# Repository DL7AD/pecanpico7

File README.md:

# Pecan Pico 7 Balloon Tracker

Pecan Pico 7 is an APRS & SSDV Tracker based on the STM32F429 microcontroller. Please note that this PCB is untested.

Components
==========

| Component                  | Description            | Purpose on PCB
| -------------------------- | ---------------------- | ----------------------------
| [**Camera OV9655 option**](https://raw.githubusercontent.com/DL7AD/pecanpico7/master/export/sch_camera.png?token=AFbk8RzoP9qTo4VENojvSboy-pLNPzOqks5Wddq2wA%3D%3D)
| TI TC1185-1.8VCT713        | LDO                    | Generate camera core voltage
| OmniVision OV9655          | Camera                 | Taking pictures
| [**Camera OV2640 option**](https://raw.githubusercontent.com/DL7AD/pecanpico7/master/export/sch_camera.png?token=AFbk8RzoP9qTo4VENojvSboy-pLNPzOqks5Wddq2wA%3D%3D)
| TI LP5951MF-1.3/NOPB       | LDO                    | Generate camera core voltage
| OmniVision OV2640          | Camera                 | Taking pictures
| [**Clock**](https://raw.githubusercontent.com/DL7AD/pecanpico7/master/export/sch_clock.png?token=AFbk8UbgKZMbE2NQFpeVvyRg0LgJKIOcks5WddrcwA%3D%3D)
| Epson TG-5006CJ-19H        | TCXO 26MHz             | Generate clock for STM32 and transceivers
| [**GNSS**](https://raw.githubusercontent.com/DL7AD/pecanpico7/master/export/sch_gps.png?token=AFbk8dw5krbUbh26B37_rMTrtYQ4tBQFks5Wddr7wA%3D%3D)
| ublox MAX-7C               | GNSS receiver          | Receive GPS or GLONASS
| Avago ALM-GP003            | Preamplifier           | Filters and preamplifies GNSS signal
| [**IO**](https://raw.githubusercontent.com/DL7AD/pecanpico7/master/export/sch_io.png?token=AFbk8fbugmLABbDKRANGqdMaBevwF8SGks5WddsRwA%3D%3D)
| *not specified*            | microSD card           | Flash memory (take any microSD card whatever you want)
| [**Micro Processor Unit (MPU)**](https://raw.githubusercontent.com/DL7AD/pecanpico7/master/export/sch_mpu.png?token=AFbk8bgT5gPxzDA8xYnTLKaIEUAItRCqks5WddshwA%3D%3D)
| STM32F429IIH6              | MCU                    | Controlling all actions on the PCB
| [**Power management**](https://raw.githubusercontent.com/DL7AD/pecanpico7/master/export/sch_power_management.png?token=AFbk8VZ4GDgAdff5pM0KQ5WDNG89CJzSks5Wdds4wA%3D%3D)
| ST SPV1040                 | Solar battery charger  | Charging the battery from solar cells
| TI TPS62260DRVT            | Step-Down regulator    | Step down voltage from battery to Vcc rail (2.5V)
| Microchip PAC1720-1-AIA-TR | Current/Voltage sensor | Measure battery input and output current and battery voltage
| [**Radios**](https://raw.githubusercontent.com/DL7AD/pecanpico7/master/export/sch_radios.png?token=AFbk8c2585z1ySrIXfuM0fE5kp1bYGUBks5WddtOwA%3D%3D)
| SiLabs Si4060 (Radio 1)    | Transmitter (2m)       | Transmitting on 2m with 3W
| rfmd RF6886                | Power amplifier        | Amplify singal from Radio 1
| SiLabs Si4464 (Radio 2)    | Transceiver (70cm)     | Transmit and Receive on 70cm with 10mW
| [**Sensing**](https://raw.githubusercontent.com/DL7AD/pecanpico7/master/export/sch_sensing.png?token=AFbk8bKAeUidCmY9ixlxbY80DIifiAG-ks5WddtfwA%3D%3D)
| Bosch BME280              | Airpressure sensor      | Measuring airpressure, humidity, temperature
| Invensense MPU-9250       | Power amplifier         | Measure acceleration, rotation, Earth's magnetic field

Bus connections to peripheral devices
=====================================

There are two I2C bus and one SPI and two UART buses available on the the PCB.
The SPI bus is dedicated to the SiLabs radios. One UART is connected to the GNSS
receiver while the other is available for external debugging purposes. There are
two additional I2C buses. One is used for the camera while the other is used for
everything else. This has been done to avoid routing the I2C through dense
regions on the PCB. The second bus of the I2C can be accessed by a pin header
for external peripheral devices such as an external BME280 to measure balloon
pressure.

**I2C**

| Bus | SCL  | SDA
| --- | ---- | ----
| 1   | PB8  | PB9
| 2   | PB10 | PB11

| Component                   | Bus | Address
| --------------------------- | --- | -------
| OmniVision OV9655/OV2640    | 1   | 0x30
| ublox MAX-7C                | 2   | 0x42
| Microchip PAC1720-1-AIA-TR  | 2   | 0x4C
| Bosch BME280                | 2   | 0x77
| Invensense MPU-9250         | 2   | 0x69
| External pin header         | 2   | -

**SPI**

- SPI SCK: PB13
- SPI MISO: PB14
- SPI MOSI: PB15

| Component                   | CS at STM32
| --------------------------- | -----------
| SiLabs Si4060 (Radio 1)     | PA11
| SiLabs Si4464 (Radio 2)     | PB0

**UART**

| Component           | STM32 TXD | STM32 RXD
| ------------------- | --------- | ---------
| uBlox MAX-7C        | PA2       | PA3
| External pin header | PA0       | PA1

Power feeding
=============

Since this tracker is designed for solar use, there's a solar charging chip, a
battery (LiPo) and a discharging regulator on it. The SPV1040 will charge the battery
on the back of the PCB. It will charge the battery up to 4.1V. The voltage of the
battery is then steped down to 2.5V by the TPS62260 which is fed by the battery. With
exception of the RF6886 All parts are fed by the 2.5V (Vcc) rail. The RF6886 is
connected directly to VBAT in order to get more power out of it. The PAC1720 is able
to measure the charge and discharge current of the battery.

**! PCB ERROR:** The PAC1720 can't measure the current consumed by RF6886.

The camera needs an addional voltage for the core. This must be 1.3V (OV2640) or 1.8V
(OV9655). Depending on which camera is used, IC10 must be changed (notes in schematic).
IC10 is switched by Q2 (GPS shutdown MOSFET). If the camera is switched off, IC10
does not get power as well.

Components Shutdown
===================

Every component has it's own shutdown capacility. Some components are switched off
by an additional MOSFET because when standard shutdown functions still need some mA.

| Component                  | Shutdown       | Notes
| -------------------------- | -------------- | --------------------------------------------
| Microchip PAC1720-1-AIA-TR | none           | Standby current 5.5uA
| Radio 1                    | Pull PA12 high |
| Radio 2                    | Pull PB12 high |
| rfmd RF6886                | none           |
| Bosch BME280               | none           | Standby current 0.2uA
| MPU-9250                   | none           | Idle mode 8uA
| Camera                     | Pull PE0 high  | Camera SHDN still draws 1mA
| Clock (TCXO)               | none           | Needed for STM32 all time
| GPS and GPS preAMP         | Pull PE7 high  |
| microSD card               | none           | SD cards have usually good internal shutdown
| STM32                      | none           |

Camera connection
=================

The camera is connected to the DCMI interface of the STM32F4 which can handle the
data though the microcontroller internally. The camera itself is connected to a FFC
connector on the PCB. The STM32 data pins are connected to

| STM32 Pin | Function
| --------- | ----------
| PA4       | DCMI_HSYNC
| PA6       | DCMI_PCLK
| PB6       | DCMI_D5
| PB7       | DCMI_VSYNC
| PC6       | DCMI_D0
| PC7       | DCMI_D1
| PC8       | DCMI_D2
| PE4       | DCMI_D3
| PB6       | DCMI_D4
| PE5       | DCMI_D6
| PE6       | DCMI_D7

Known PCB errors
================

**ERROR 1:** RF6886 connected incorrectly to PAC1720 (fixable)<br />
Effect: PAC1720 can't measure the current consumed by RF6886<br />
Solution: *none* (will be fixed on next revision)

**ERROR 2:** Capacitor missing at TPS62260DRVT (fixable)<br />
Effect: This capacitor is responsible to reduce voltage ripple on Vcc rail.<br />
Solution: Solder a capacitor (22pF 0402) on top of R18

**ERROR 3:** BYPASS_REG connected to Vcc (fixable)<br />
Effect: The STM32 doesn't starup because internal voltage regulate is shut down<br />
Solution: Desolder R41 and connect BYPASS_REG to GND (put solder junction to resistor pad next to R41)

**ERROR 4:** Wrong oscillator only supplies 0.7V (fixable)<br />
Effect: The external oscillator can't be used for the STM32<br />
Solution: Use ~~an TXC 7L 26MHz oscillator instead or~~ use the internal oscillator
See: Error 7

**ERROR 5:** Camera connector swapped (fixable)<br />
Pin 1 should be actually Pin 24 and Pin 24 should be Pin 1
Effect: The camera and the core voltage segulator gets very hot<br />
Solution: Solder the camera to the PCB upsidedown (not easy but possible)

**ERROR 6:** LED6 - 9 anode and cathode switched (fixable)<br />
Effect: The LED's will not work<br />
Solution: Ignore the LED-soldermask and solder them in the other way around

**ERROR 7:** External oscillator connected to OSC32_IN instead of OSC_IN (not fixable)<br />
Effect: The external HSE oscillator can't be used for clocking<br />
Solution: Use the internal clock (HSI), Problem => HSI very inaccurate (~5%)

**WARNING 1:** LEDs connected to transceivers are switched on<br />
Effect: Current draw on startup. It could prevent the PCB to startup when the battery is dischanged completely, when the SPV1040 doesn't provide enough power. So the STM32 doesnt boot.<br />
Solution: *none* (will be fixed on next revision) or desolder LEDs

**WARNING 2:** Pad extremly large on PAC1720 and MPU9250<br />
Effect: It could cause solder junctions in production<br />
Solution: *none* (will be fixed on next revision) or put less solder on the pads

**WARNING 3:** Solder jumper included in soldermask<br />
Effect: *no electrical effect*<br />
Solution: *none* (will be fixed on next revision)

**WARNING 4:** RF6886 draws much current in idle<br />
Effect: *no functional limitation*<br />
Solution: *none* (will be fixed on next revision)

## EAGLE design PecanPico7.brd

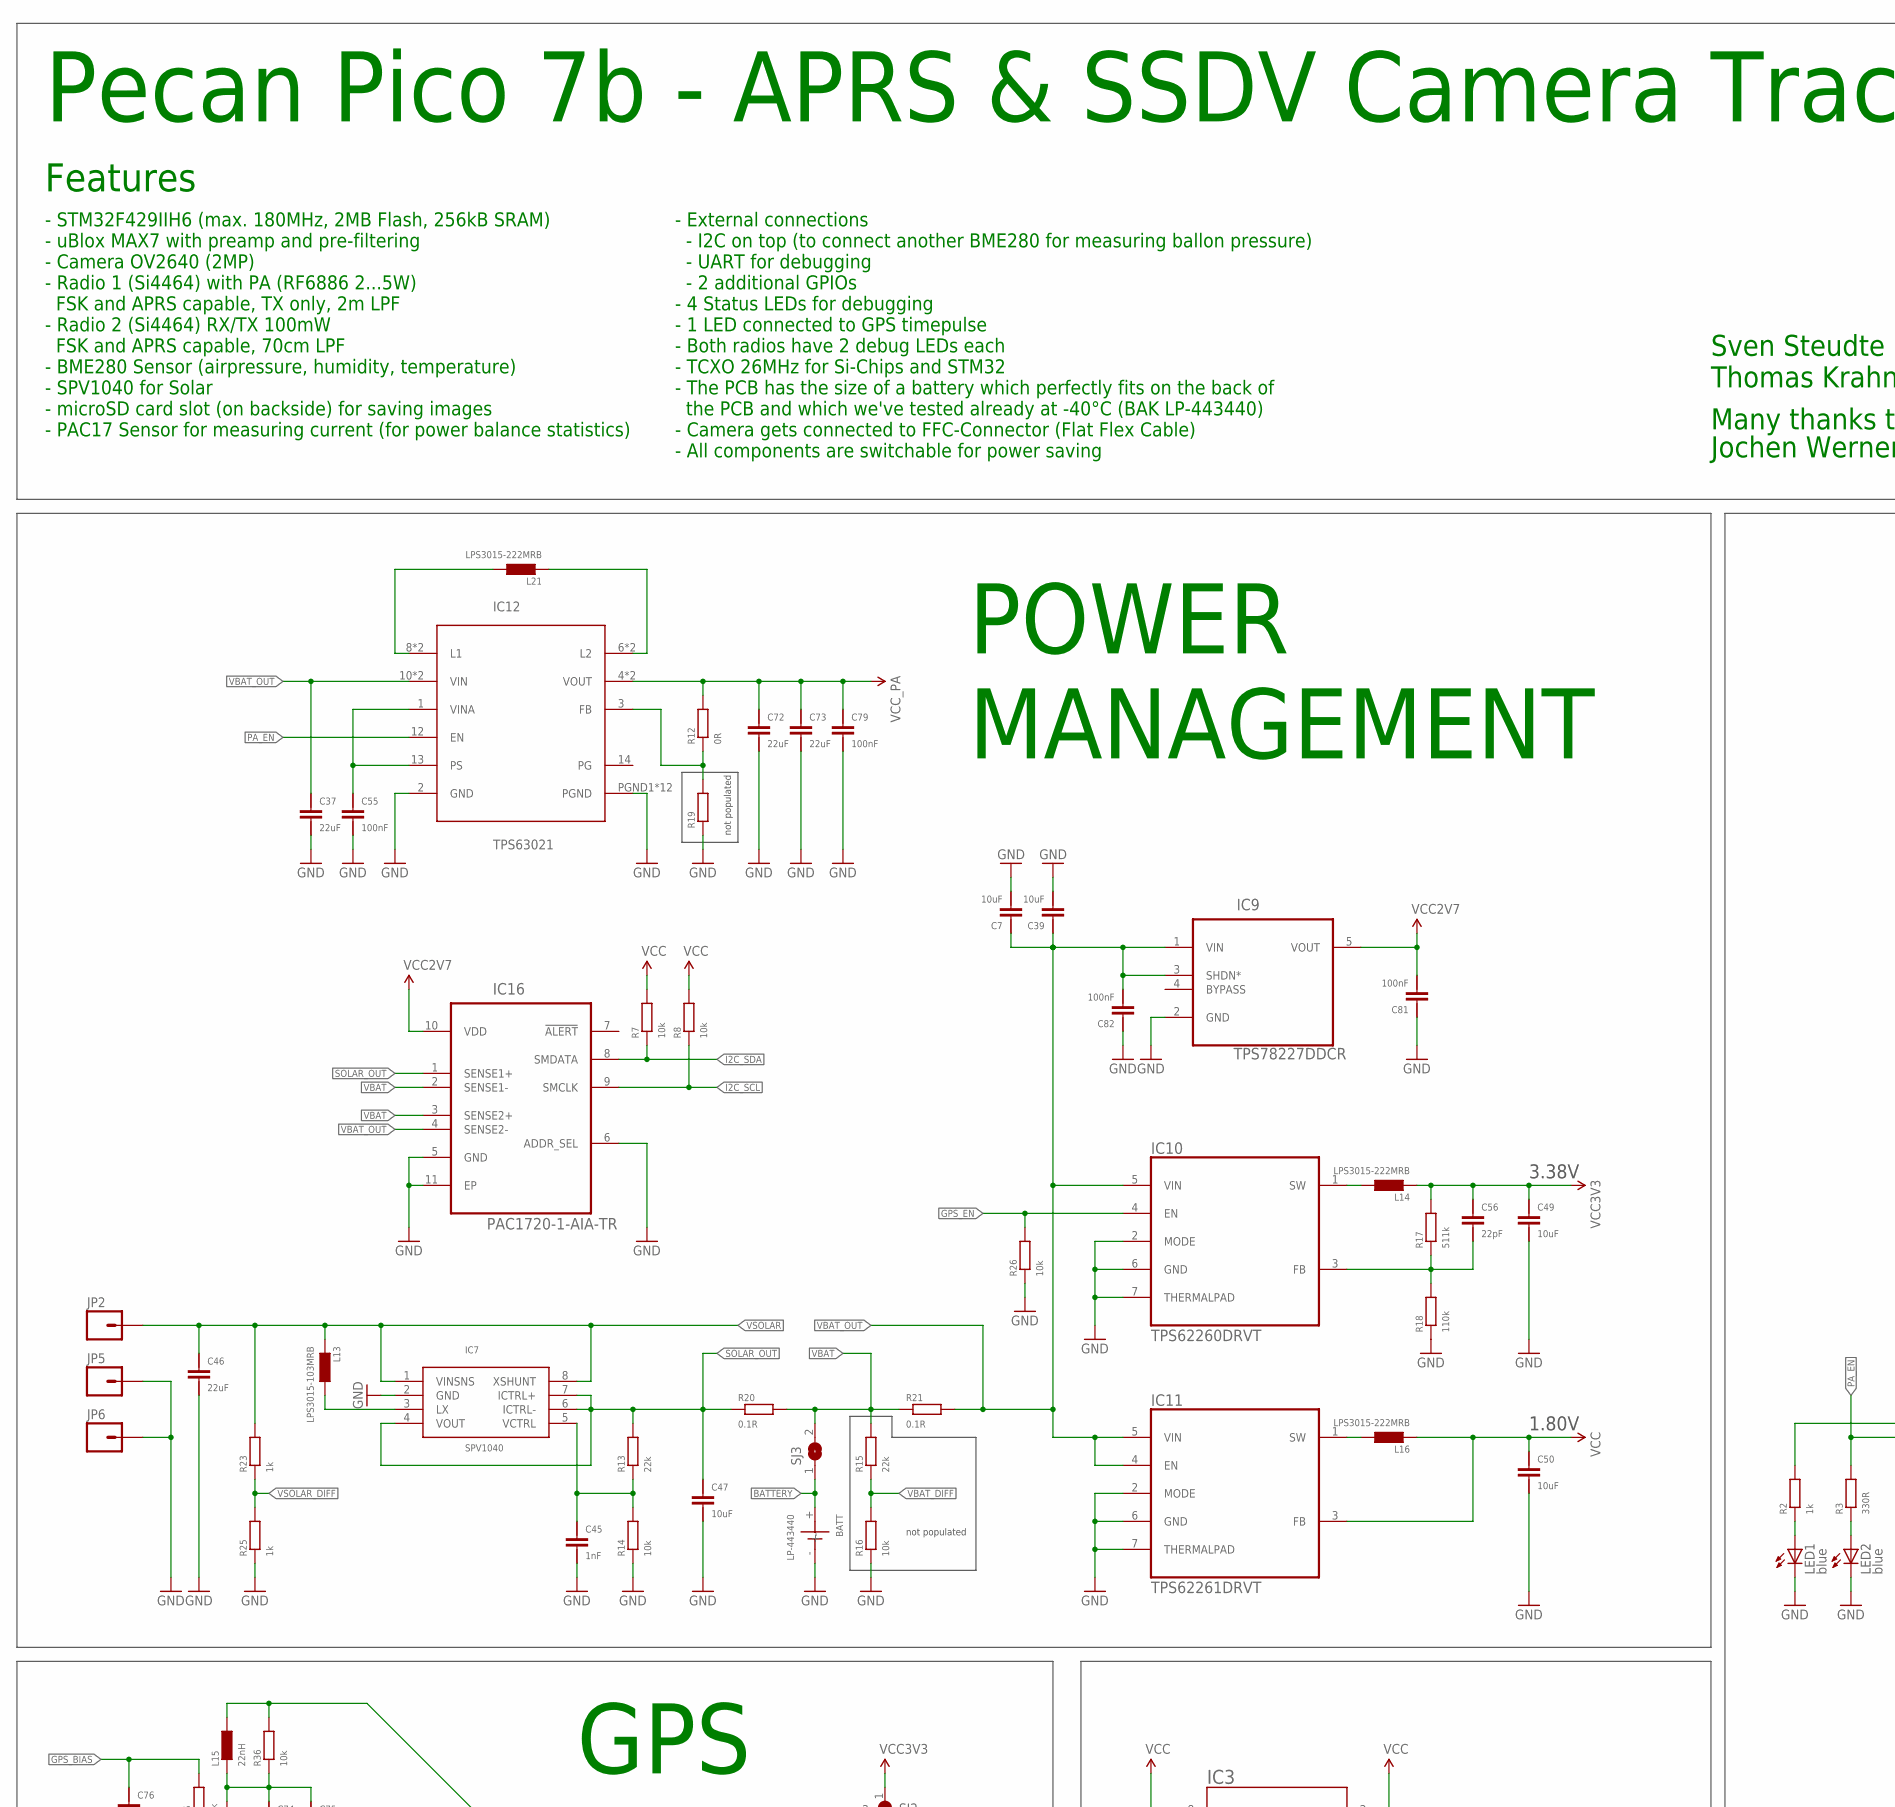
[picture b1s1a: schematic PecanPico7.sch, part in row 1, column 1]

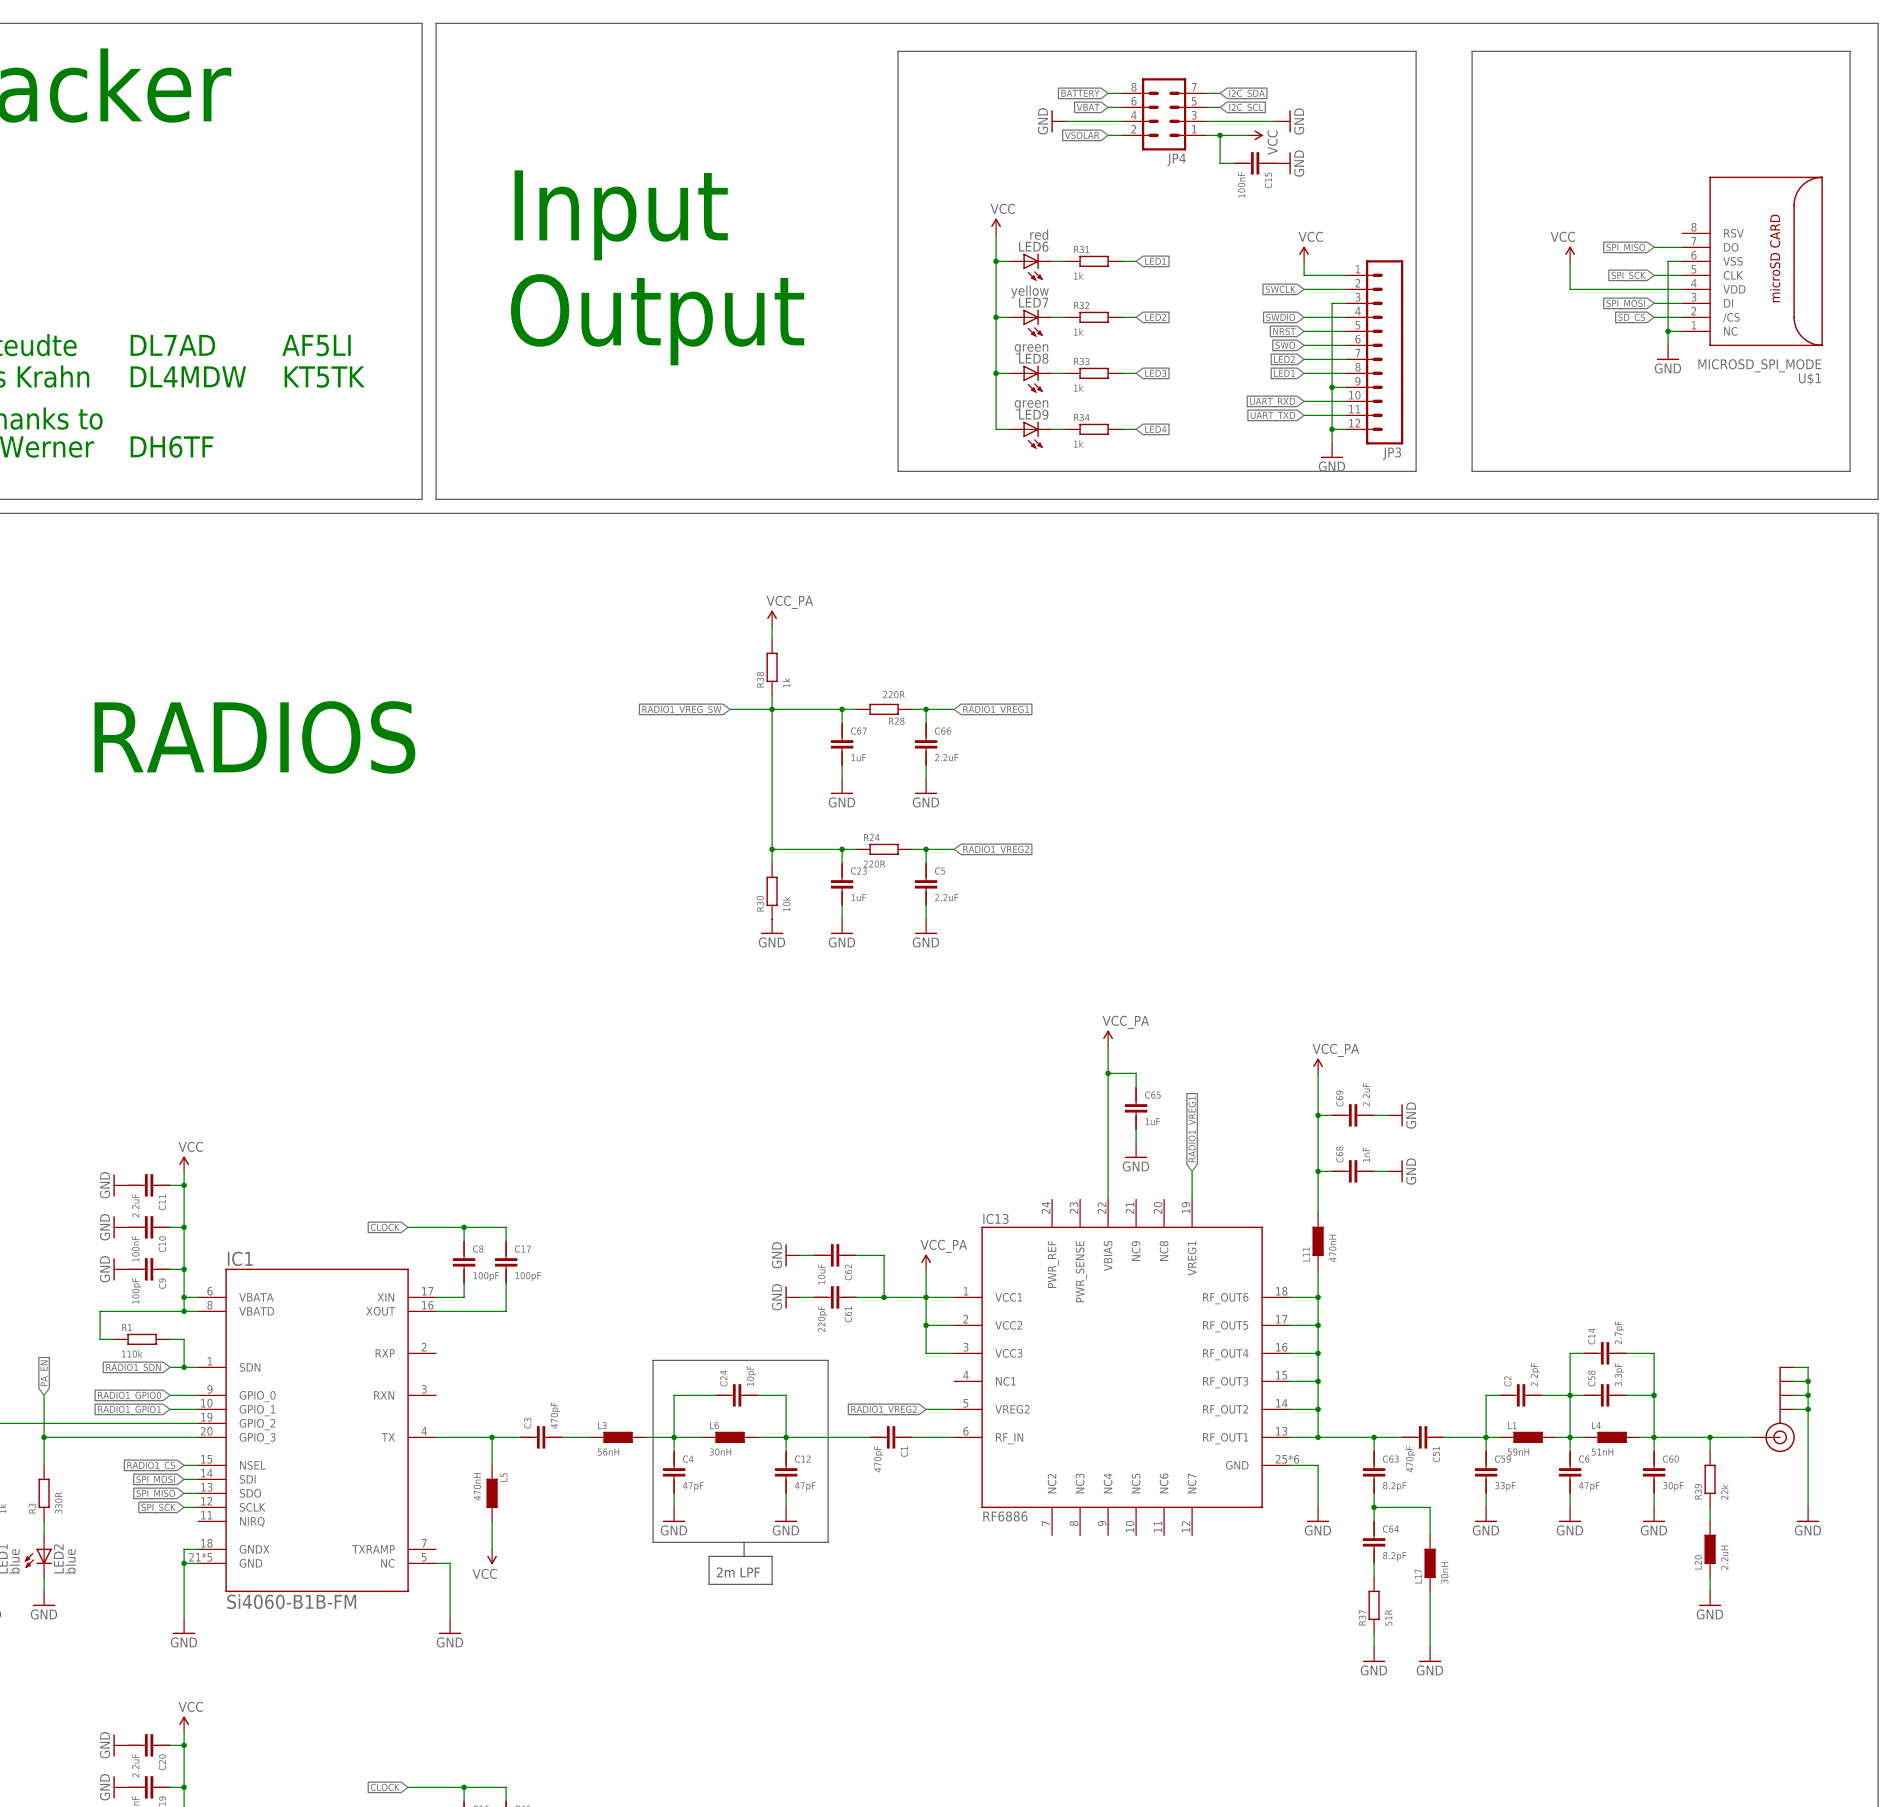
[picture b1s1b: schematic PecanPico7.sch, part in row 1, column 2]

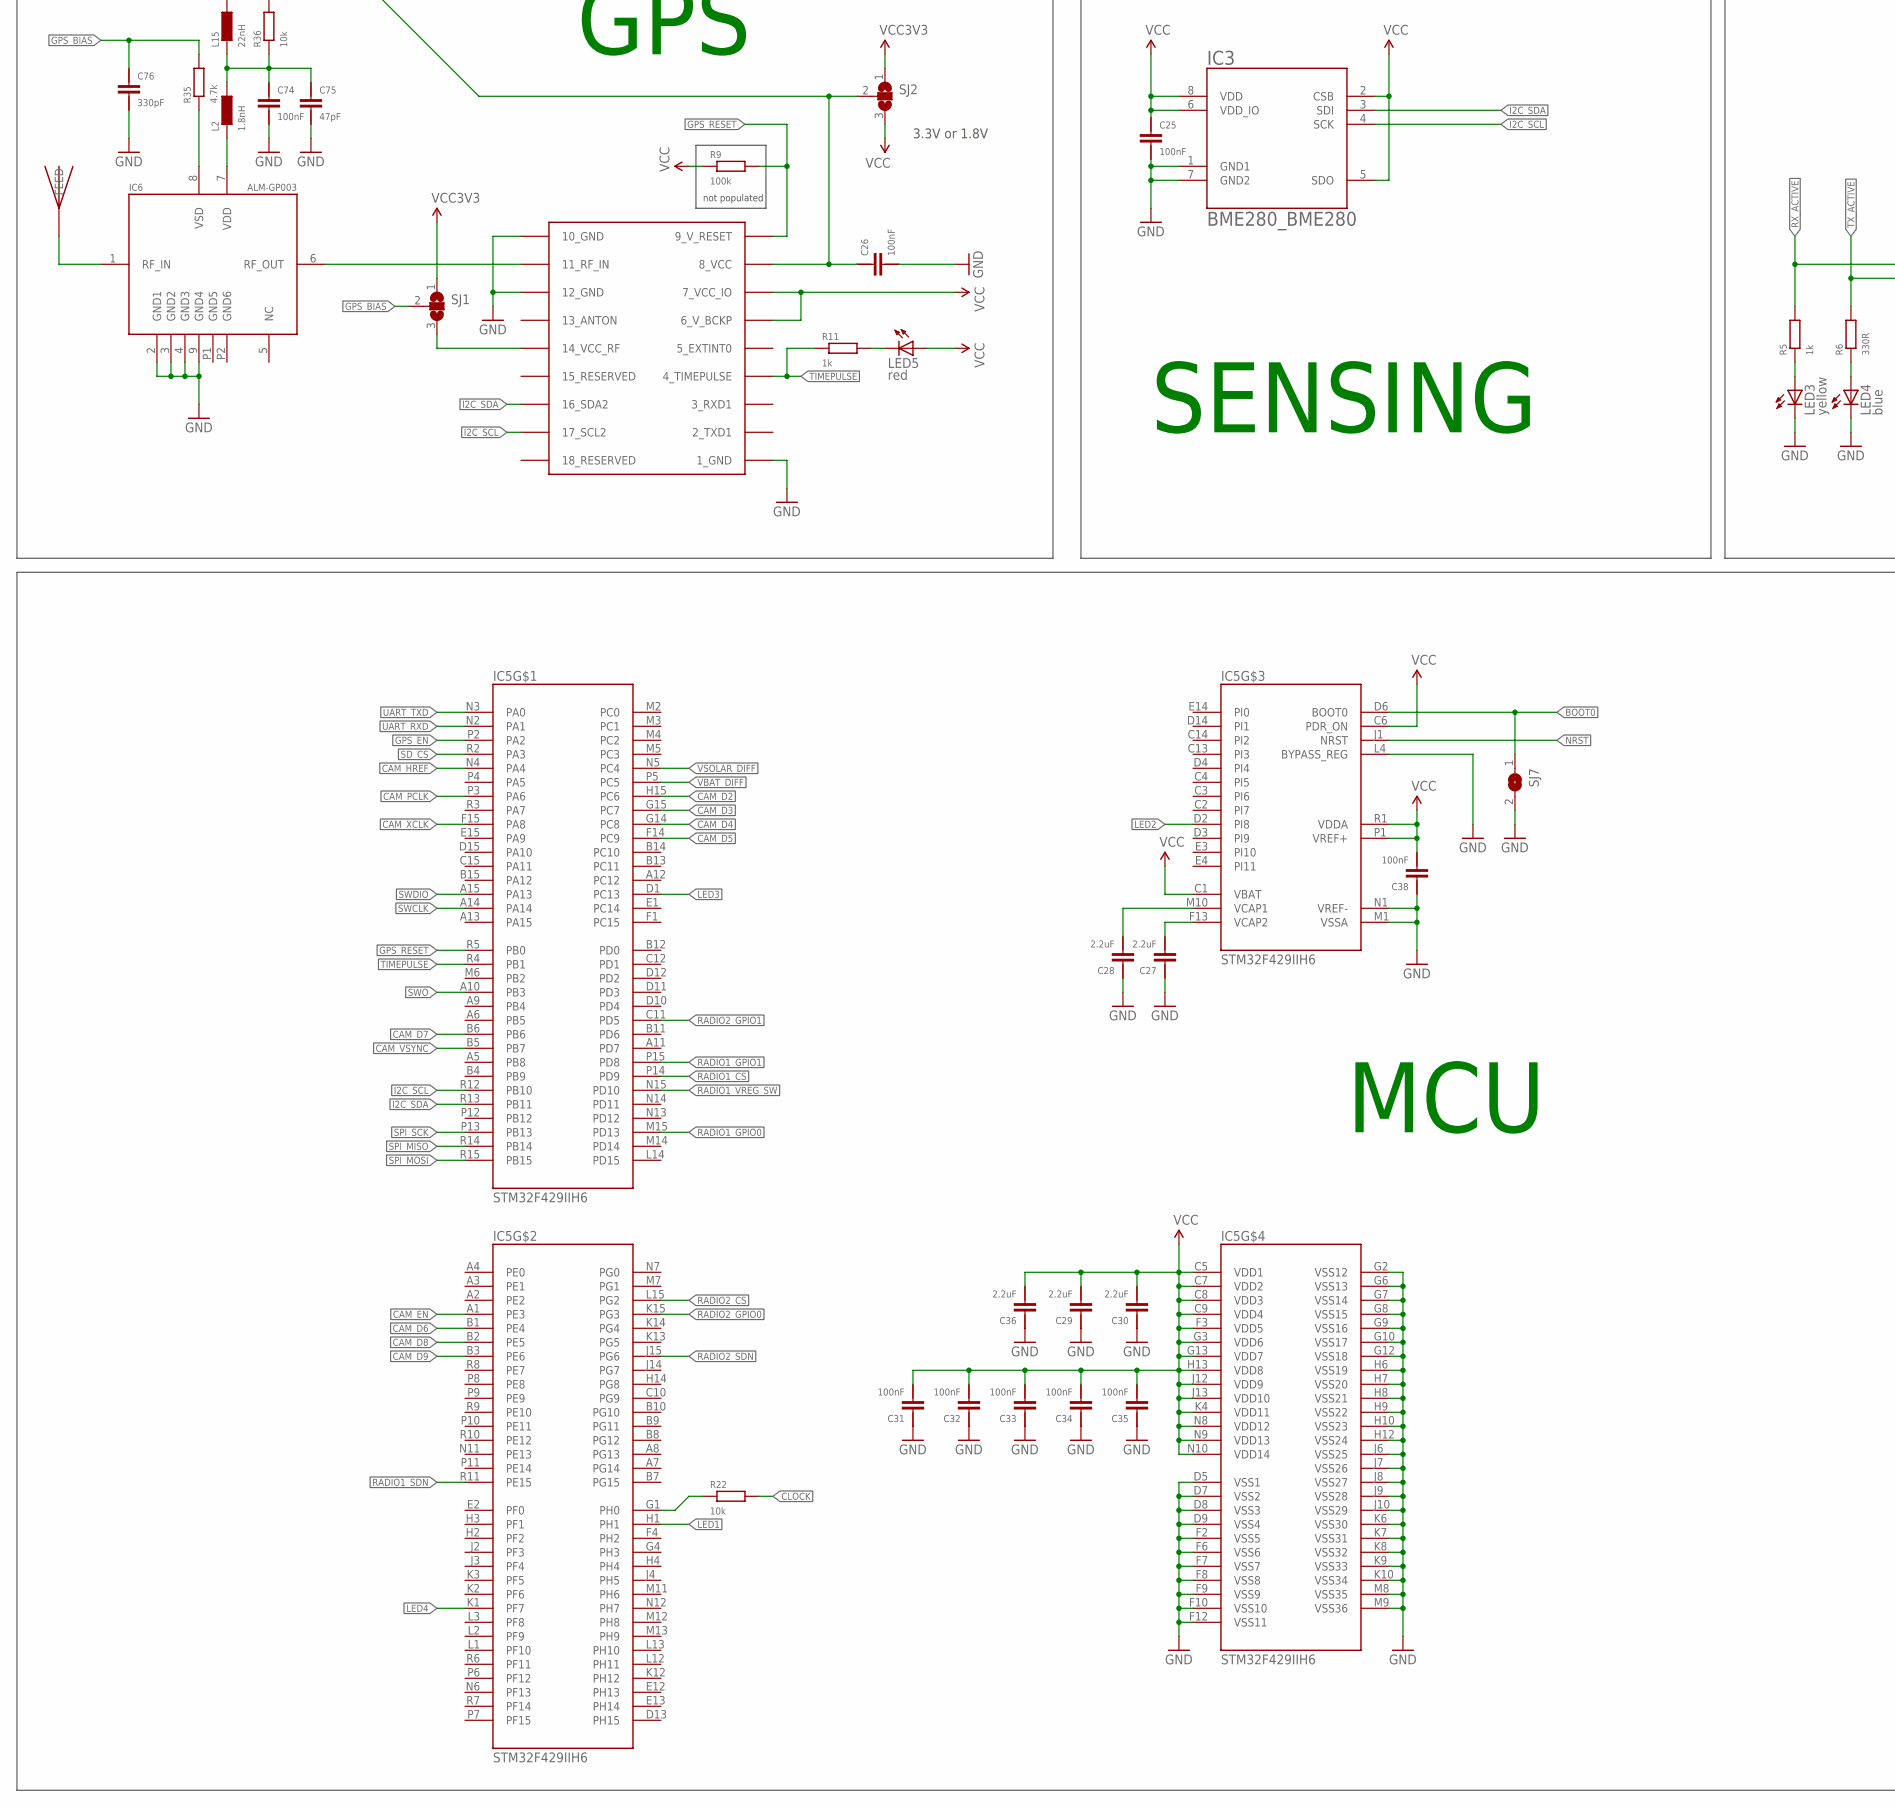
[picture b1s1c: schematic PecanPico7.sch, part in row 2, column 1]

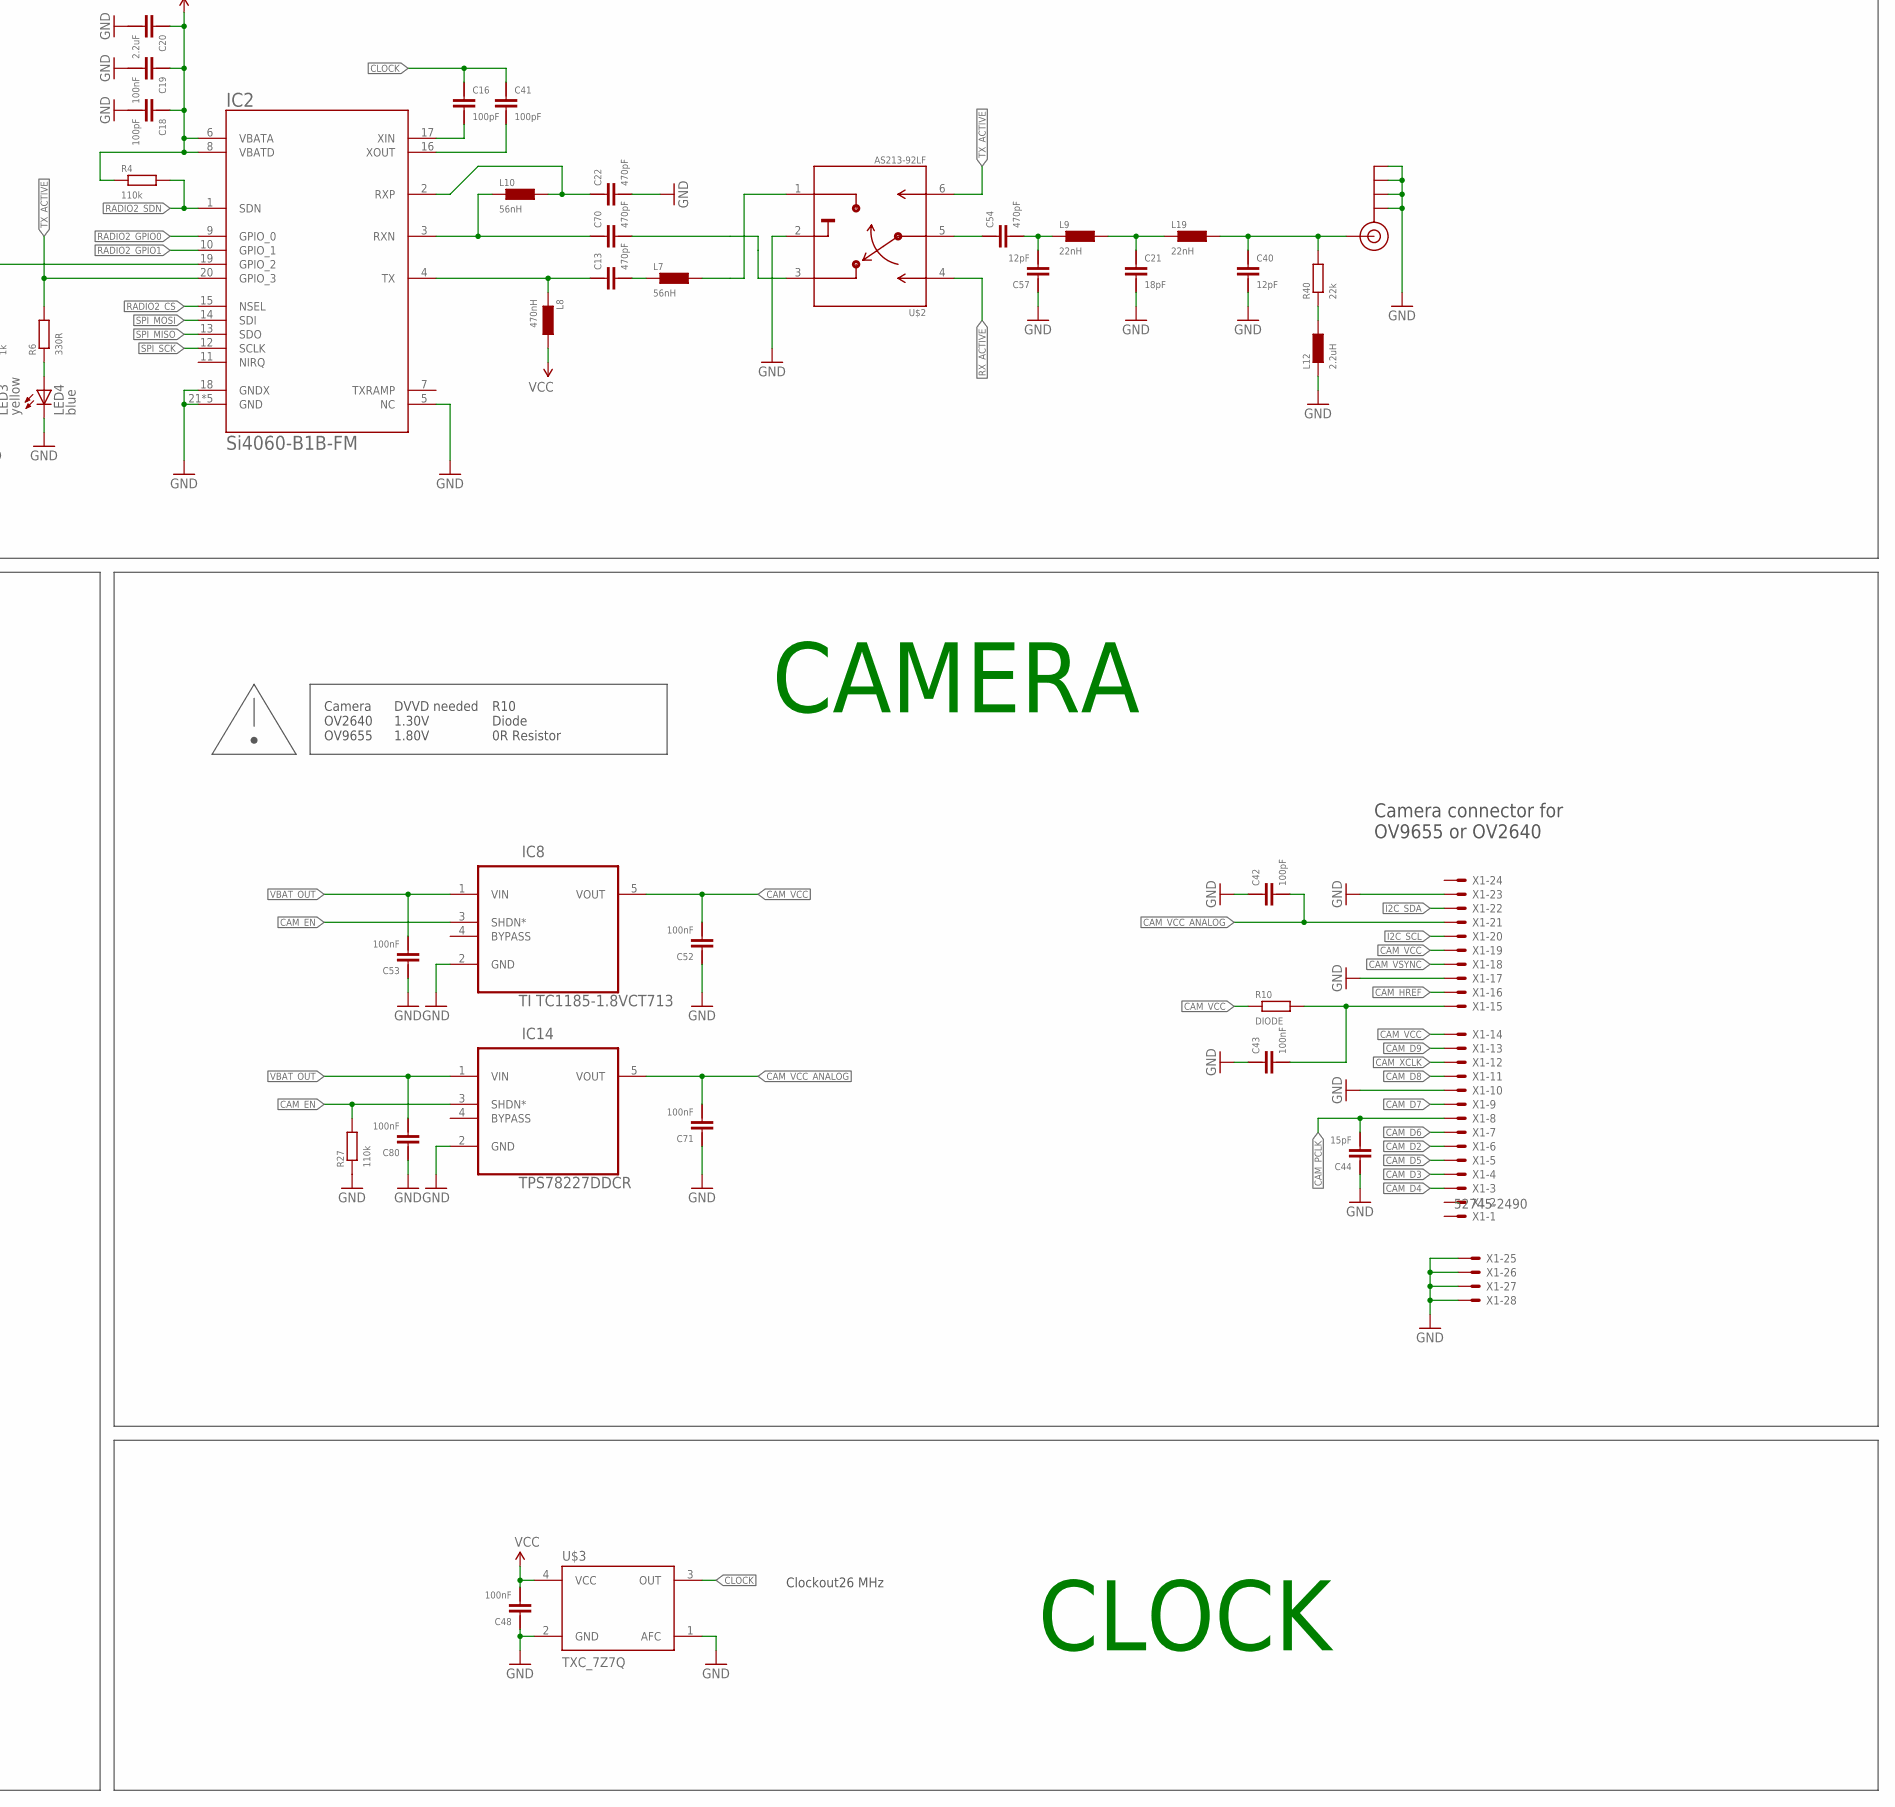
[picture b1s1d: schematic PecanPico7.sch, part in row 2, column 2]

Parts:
BATT: LP-443440
C1, C3, C13, C22, C51, C54, C70: 470pF; 0402
C2: 2.2pF; 0402
C4, C6, C12, C75: 47pF; 0402
C5, C11, C20, C27, C28, C29, C30, C36, C66, C69: 2.2uF; 0402
C7, C39, C47, C49, C50, C62: 10uF; 0805
C8, C9, C16, C17, C18, C41, C42: 100pF; 0402
C10, C15, C19, C25, C26, C31, C32, C33, C34, C35, C38, C43, C48, C52, C53, C55, C71, C74, C79, C80, C81, C82: 100nF; 0402
C14: 2.7pF; 0402
C21: 18pF; 0402
C23, C65, C67: 1uF; 0402
C24: 10pF; 0402
C37, C46, C72, C73: 22uF; 0805
C40, C57: 12pF; 0402
C44: 15pF; 0402
C45, C68: 1nF; 0402
C56: 22pF; 0402
C58: 3.3pF; 0402
C59: 33pF; 0402
C60: 30pF; 0402
C61: 220pF; 0402
C63, C64: 8.2pF; 0402
C76: 330pF; 0402
IC1, IC2: Si4060-B1B-FM; QFN-20
IC3: BME280_BME280
IC4: uBlox MAX7/8; UBLOX_MAX-6
IC5: STM32F429IIH6; UFBGA176
IC6: ALM-GP003
IC7: SPV1040; TSSOP8
IC8: TI TC1185-1.8VCT713; SOT95P290X145-5N
IC9, IC14: TPS78227DDCR; SOT95P290X145-5N
IC10: TPS62260DRVT; SON65P210X210X80-7N
IC11: TPS62261DRVT; SON65P210X210X80-7N
IC12: TPS63021; QFN-14
IC13: RF6886; QFN-24
IC16: PAC1720-1-AIA-TR; DFN300X300X90-11N
J$1, J$2: SMA_EDGE; SMA-EDGE
JP2, JP5, JP6: M01SMD; LUXEON-PAD
JP3: M12PTH; 1X12
JP4: M04X2SMD; 2X4_2
L1: 59nH; 0603@1
L2: 1.8nH; 0402
L3, L7, L10: 56nH; 0402
L4: 51nH; 0603@1
L5, L8, L11: 470nH; 0805@1
L6: 30nH; 0402
L9, L15, L19: 22nH; 0402
L12, L20: 2.2uH; 0402
L13: LPS3015-103MRB; LPS3015
L14, L16, L21: LPS3015-222MRB; LPS3015
L17: 30nH; 0603@1
LED1, LED2, LED4: blue; LED-0603
LED3, LED7: yellow; LED-0603
LED5, LED6: red; LED-0603
LED8, LED9: green; LED-0603
R1, R4, R18, R27: 110k; 0402
R2, R5, R11, R23, R25, R31, R32, R33, R34, R38: 1k; 0402
R3, R6: 330R; 0402
R7, R8, R14, R16, R22, R26, R30, R36: 10k; 0402
R9: 100k; 0402
R10: DIODE; 0402
R12: 0R; 0402
R13, R15, R39, R40: 22k; 0402
R17: 511k; 0402
R19: RES-0402; 0402
R20, R21: 0.1R; 0603
R24, R28: 220R; 0402
R35: 4.7k; 0402
R37: 51R; 0402
SJ1, SJ2: SJ2W; SJ_2
SJ3, SJ7: SJ
U$1: MICROSD_SPI_MODE; MICRO_SD_CONNECTOR
U$2: AS213-92LF; SC-70
U$3: TXC_7Z7Q; TCXO_3.2X2.5
U$4: JTI_ANTENNA-1575AT43A40
X1: 52745-2490

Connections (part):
BATTERY: BATT.+, JP4.8, SJ3.1
BOOT0: IC5.D6 (BOOT0), SJ7.1
CAM_D2: IC5.H15 (PC6), X1.6
CAM_D3: IC5.G15 (PC7), X1.4
CAM_D4: IC5.G14 (PC8), X1.3
CAM_D5: IC5.F14 (PC9), X1.5
CAM_D6: IC5.B1 (PE4), X1.7
CAM_D7: IC5.B6, X1.9
CAM_D8: IC5.B2 (PE5), X1.11
CAM_D9: IC5.B3 (PE6), X1.13
CAM_EN: IC5.A1 (PE3), IC8.3 (SHDN*), IC14.3 (SHDN*), R27.P$2 (2)
CAM_HREF: IC5.N4 (PA4), X1.16
CAM_PCLK: C44.P$1 (1), IC5.P3 (PA6), X1.8
CAM_VCC: C52.P$1 (1), IC8.5 (VOUT), R10.P$1 (1), X1.14, X1.19
CAM_VCC_ANALOG: C42.P$1 (1), C71.P$1 (1), IC14.5 (VOUT), X1.21
CAM_VSYNC: IC5.B5 (PB7), X1.18
CAM_XCLK: IC5.F15 (PA8), X1.12
CLOCK: C8.P$2 (2), C16.P$2 (2), C17.P$2 (2), C41.P$2 (2), R22.P$2 (2), U$3.3 (OUT)
GND: BATT.-, C4.P$1 (1), C5.P$1 (1), C6.P$1 (1), C7.1, C9.P$1 (1), C10.P$1 (1), C11.P$1 (1), C12.P$1 (1), C15.P$2 (2), C18.P$1 (1), C19.P$1 (1), C20.P$1 (1), C21.P$1 (1), C22.P$1 (1), C23.P$1 (1), C25.P$1 (1), C26.P$1 (1), C27.P$2 (2), C28.P$2 (2), C29.P$2 (2), C30.P$2 (2), C31.P$2 (2), C32.P$2 (2), C33.P$2 (2), C34.P$2 (2), C35.P$2 (2), C36.P$2 (2), C37.1, C38.P$2 (2), C39.1, C40.P$1 (1), C42.P$2 (2), C43.P$2 (2), C44.P$2 (2), C45.P$1 (1), C46.1, C47.1, C48.P$2 (2), C49.1, C50.1, C52.P$2 (2), C53.P$2 (2), C55.P$1 (1), C57.P$2 (2), C59.P$1 (1), C60.P$1 (1), C61.P$1 (1), C62.1, C65.P$1 (1), C66.P$1 (1), C67.P$1 (1), C68.P$1 (1), C69.P$1 (1), C71.P$2 (2), C72.1, C73.1, C74.P$1 (1), C75.P$1 (1), C76.P$1 (1), C79.P$1 (1), C80.P$2 (2), C81.P$2 (2), C82.P$2 (2), IC1.5 (NC), IC1.18 (GNDX), IC1.21 (GND), IC1.22 (GND), IC1.23 (GND), IC1.24 (GND), IC1.25 (GND), IC2.5 (NC), IC2.18 (GNDX), IC2.21 (GND), IC2.22 (GND), IC2.23 (GND), IC2.24 (GND), IC2.25 (GND), IC3.1 (GND1), IC3.7 (GND2), IC4.1_GND, IC4.10_GND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
GPS_BIAS: C76.P$2 (2), R35.P$2 (2), SJ1.2
GPS_EN: IC5.P2 (PA2), IC10.4 (EN), R26.P$2 (2)
GPS_RESET: IC4.9_V_RESET, IC5.R5 (PB0), R9.P$2 (2)
I2C_SCL: IC3.4 (SCK), IC4.17_SCL2, IC5.R12 (PB10), IC16.9 (SMCLK), JP4.5, R8.P$1 (1), X1.20
I2C_SDA: IC3.3 (SDI), IC4.16_SDA2, IC5.R13 (PB11), IC16.8 (SMDATA), JP4.7, R7.P$1 (1), X1.22
LED1: IC5.H1, JP3.8, R31.P$2 (2)
LED2: IC5.D2 (PI8), JP3.7, R32.P$2 (2)
LED3: IC5.D1 (PC13), R33.P$2 (2)
LED4: IC5.K1 (PF7), R34.P$2 (2)
unnamed: C4.P$2 (2), C24.P$2 (2), L3.P$2 (2), L6.P$1 (1)
unnamed: C3.P$2 (2), IC1.4 (TX), L5.P$1 (1)
unnamed: C3.P$1 (1), L3.P$1 (1)
unnamed: C70.P$2 (2), IC2.3 (RXN), L10.P$1 (1)
unnamed: C2.P$1 (1), C6.P$2 (2), C14.P$2 (2), C58.P$2 (2), L1.P$2 (2), L4.P$1 (1)
unnamed: C1.P$2 (2), IC13.6 (RF_IN)
unnamed: IC6.1 (RF_IN), U$4.FEED
unnamed: C2.P$2 (2), C51.P$2 (2), C59.P$2 (2), L1.P$1 (1)
unnamed: C17.P$1 (1), IC1.16 (XOUT)
unnamed: C1.P$1 (1), C12.P$2 (2), C24.P$1 (1), L6.P$2 (2)
unnamed: L7.P$2 (2), U$2.1 (B2)
unnamed: C43.P$1 (1), R10.P$2 (2), X1.15
unnamed: IC1.19 (GPIO_2), R2.P$2 (2)
unnamed: C13.P$2 (2), IC2.4 (TX), L8.P$1 (1)
unnamed: C13.P$1 (1), L7.P$1 (1)
unnamed: C63.P$1 (1), C64.P$2 (2), L17.P$2 (2)
unnamed: C16.P$1 (1), IC2.17 (XIN)
unnamed: C41.P$1 (1), IC2.16 (XOUT)
unnamed: LED3.A, R5.P$1 (1)
unnamed: LED1.A, R2.P$1 (1)
unnamed: LED2.A, R3.P$1 (1)
unnamed: LED4.A, R6.P$1 (1)
unnamed: C64.P$1 (1), R37.P$2 (2)
unnamed: C21.P$2 (2), L9.P$2 (2), L19.P$1 (1)
unnamed: C70.P$1 (1), U$2.3 (B1)
unnamed: LED5.C, R11.P$2 (2)
unnamed: C56.P$1 (1), IC10.3 (FB), R17.P$1 (1), R18.P$2 (2)
unnamed: C40.P$2 (2), J$2.SIG (SIGNAL), L19.P$2 (2), R40.P$2 (2)
unnamed: IC10.1 (SW), L14.2_1 (2), L14.2_2 (2), L14.2_3 (2), L14.2_4 (2), L14.2_5 (2), L14.2_6 (2), L14.2_7 (2), L14.2_8 (2), L14.2_9 (2)
unnamed: IC11.1 (SW), L16.2_1 (2), L16.2_2 (2), L16.2_3 (2), L16.2_4 (2), L16.2_5 (2), L16.2_6 (2), L16.2_7 (2), L16.2_8 (2), L16.2_9 (2)
unnamed: C45.P$2 (2), IC7.5 (VCTRL), R13.P$1 (1), R14.P$2 (2)
unnamed: IC4.11_RF_IN, IC6.6 (RF_OUT)
unnamed: C27.P$1 (1), IC5.F13 (VCAP2)
unnamed: C28.P$1 (1), IC5.M10 (VCAP1)
unnamed: C8.P$1 (1), IC1.17 (XIN)
unnamed: IC7.3 (LX), L13.2_1 (2), L13.2_2 (2), L13.2_3 (2), L13.2_4 (2), L13.2_5 (2), L13.2_6 (2), L13.2_7 (2), L13.2_8 (2), L13.2_9 (2)
unnamed: IC5.G1 (PH0), R22.P$1 (1)
unnamed: C26.P$2 (2), IC4.8_VCC, L15.P$2 (2), R36.P$2 (2), SJ2.2
unnamed: C14.P$1 (1), C58.P$1 (1), C60.P$2 (2), J$1.SIG (SIGNAL), L4.P$2 (2), R39.P$2 (2)
unnamed: LED7.C, R32.P$1 (1)
unnamed: C51.P$1 (1), C63.P$2 (2), IC13.13 (RF_OUT1), IC13.14 (RF_OUT2), IC13.15 (RF_OUT3), IC13.16 (RF_OUT4), IC13.17 (RF_OUT5), IC13.18 (RF_OUT6), L11.P$1 (1)
unnamed: IC12.8 (L1), IC12.9 (L1), L21.2_1 (2), L21.2_2 (2), L21.2_3 (2), L21.2_4 (2), L21.2_5 (2), L21.2_6 (2), L21.2_7 (2), L21.2_8 (2), L21.2_9 (2)
unnamed: IC6.8 (VSD), R35.P$1 (1)
unnamed: IC6.7 (VDD), L2.P$1 (1)
unnamed: LED8.C, R33.P$1 (1)
unnamed: LED9.C, R34.P$1 (1)
unnamed: LED6.C, R31.P$1 (1)
unnamed: IC12.6 (L2), IC12.7 (L2), L21.1_1 (1), L21.1_2 (1), L21.1_3 (1), L21.1_4 (1), L21.1_5 (1), L21.1_6 (1), L21.1_7 (1), L21.1_8 (1), L21.1_9 (1)
unnamed: C74.P$2 (2), C75.P$2 (2), L2.P$2 (2), L15.P$1 (1), R36.P$1 (1)
unnamed: IC4.14_VCC_RF, SJ1.3
unnamed: C22.P$2 (2), IC2.2 (RXP), L10.P$2 (2)
unnamed: L20.P$2 (2), R39.P$1 (1)
unnamed: C54.P$2 (2), U$2.5 (A1)
unnamed: C54.P$1 (1), C57.P$1 (1), L9.P$1 (1)
unnamed: L12.P$2 (2), R40.P$1 (1)
unnamed: IC12.3 (FB), R12.P$1 (1), R19.P$2 (2)
unnamed: C55.P$2 (2), IC12.1 (VINA), IC12.13 (PS)
NRST: IC5.J1 (NRST), JP3.5
PA_EN: IC1.20 (GPIO_3), IC12.12 (EN), R3.P$2 (2)
RADIO1_CS: IC1.15 (NSEL), IC5.P14 (PD9)
RADIO1_GPIO0: IC1.9 (GPIO_0), IC5.M15 (PD13)
RADIO1_GPIO1: IC1.10 (GPIO_1), IC5.P15 (PD8)
RADIO1_SDN: IC1.1 (SDN), IC5.R11 (PE15), R1.P$2 (2)
RADIO1_VREG1: C66.P$2 (2), IC13.19 (VREG1), R28.P$1 (1)
RADIO1_VREG2: C5.P$2 (2), IC13.5 (VREG2), R24.P$2 (2)
RADIO1_VREG_SW: C23.P$2 (2), C67.P$2 (2), IC5.N15 (PD10), R24.P$1 (1), R28.P$2 (2), R30.P$2 (2), R38.P$1 (1)
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
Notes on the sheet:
CLOCK
CAMERA
RADIOS
POWER MANAGEMENT
GPS
SENSING
MCU
Pecan Pico 7b - APRS & SSDV Camera Tracker
Input Output
Sven Steudte Thomas Krahn
DL7AD DL4MDW
AF5LI KT5TK
- STM32F429IIH6 (max. 180MHz, 2MB Flash, 256kB SRAM) - uBlox MAX7 with preamp and pre-filtering - Camera OV2640 (2MP) - Radio 1 (Si4464) with PA (RF6886 2...5W) FSK and APRS capable, TX only, 2m LPF - Radio 2 (Si4464) RX/TX 100mW FSK and APRS capable, 70cm LPF - BME280 Sensor (airpressure, humidity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
- External connections - I2C on top (to connect another BME280 for measuring ballon pressure) - UART for debugging - 2 additional GPIOs - 4 Status LEDs for debugging - 1 LED connected to GPS timepulse - Both radios have 2 debug LEDs each - TCXO 26MHz for Si-Chips and STM32 - The PCB has the size of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
Features
Camera OV2640 OV9655
DVVD needed 1.30V 1.80V
R10 Diode 0R Resistor
Camera connector for OV9655 or OV2640
Clockout26 MHz
2m LPF
3.3V or 1.8V
1.80V
3.38V
not populated
Many thanks to
Jochen Werner
DH6TF

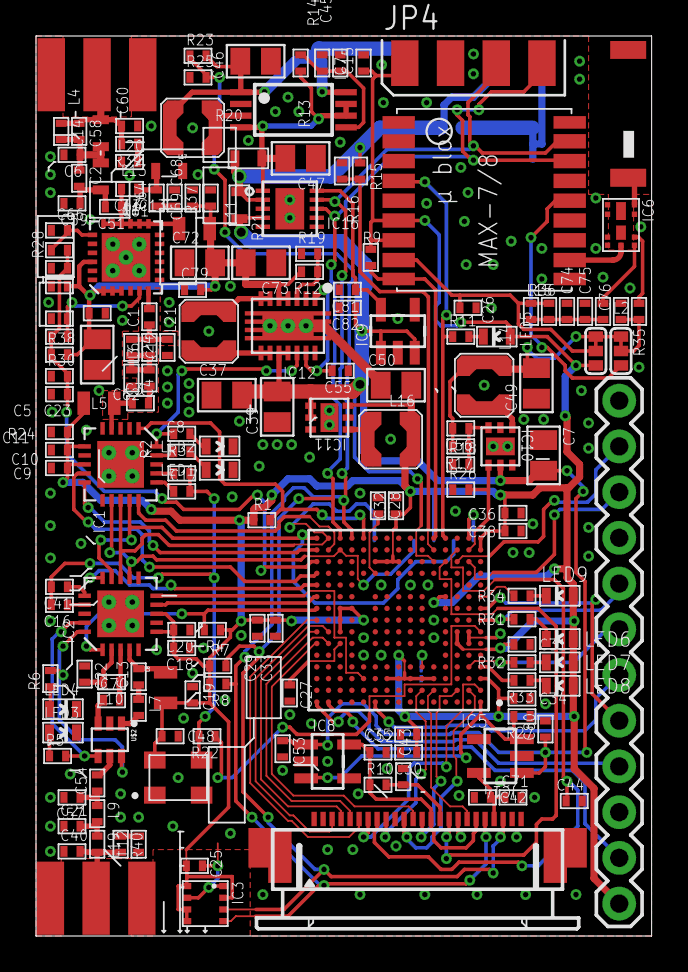
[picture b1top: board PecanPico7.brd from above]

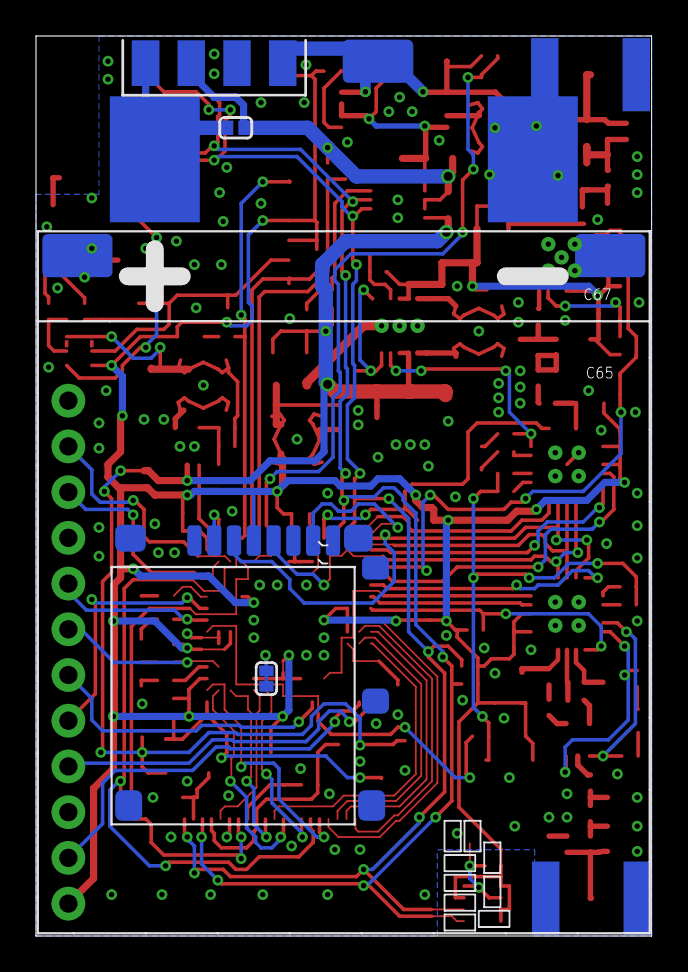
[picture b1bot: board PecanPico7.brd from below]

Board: 2 copper layers, 34.2 x 50.0 mm, 180 parts (7 on the bottom side), 120 nets.

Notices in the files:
parts and their libraries:
SparkFun-Connectors: Licensing: Creative Commons ShareAlike 4.0 International - https://creativecommons.org/licenses/by-sa/4.0
